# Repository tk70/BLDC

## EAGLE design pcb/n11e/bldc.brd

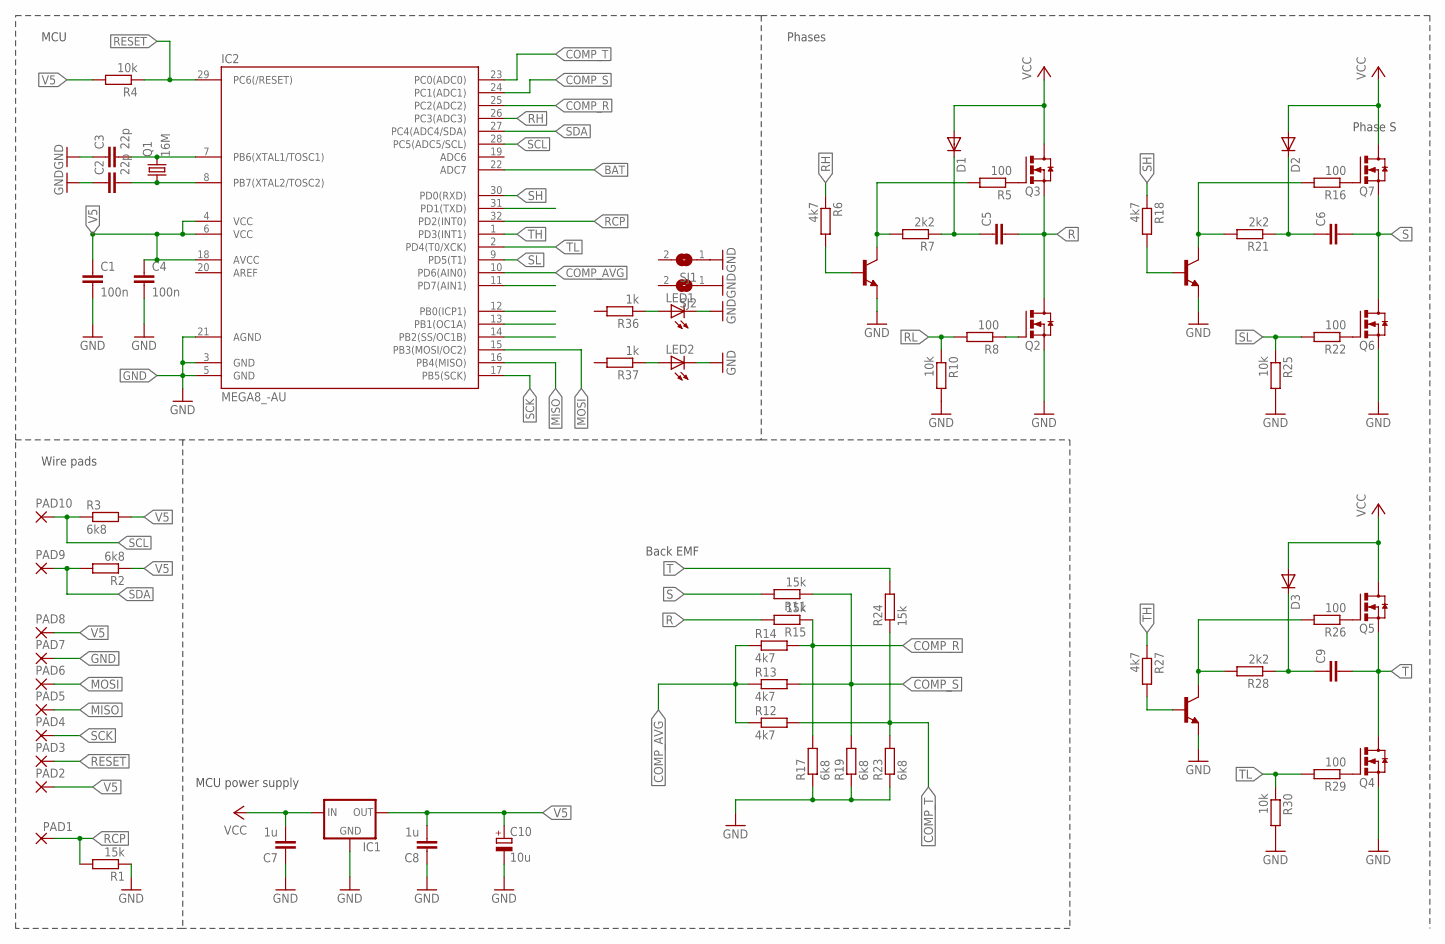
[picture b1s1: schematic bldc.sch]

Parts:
C1, C4: 100n; C0805K
C2, C3: 22p; C0805K
C5, C6, C9: C-EUC1206K; C1206K
C7, C8: 1u; C0805K
C10: 10u; E2,5RE
D1, D2, D3: 1N4148SOD-80; C1206K
IC1: LM1117TO252; TO252
IC2: MEGA8_-AU; TQFP32-08
LED1, LED2: LEDCHIPLED_0805; CHIPLED_0805
PAD1, PAD2, PAD3, PAD4, PAD5, PAD6, PAD7, PAD8, PAD9, PAD10: WIREPADSMD1,27-254; SMD1,27-2,54
Q1: 16M; SM49
Q2, Q3, Q4, Q5, Q6, Q7: IRFR1205; D-PAK_TO252AA
R1, R11, R24: 15k; R0603
R2, R3, R17, R19, R23: 6k8; R0603
R4, R10, R25, R30: 10k; R0603
R5, R8, R16, R22, R26, R29: 100; R0603
R6, R12, R13, R14, R18, R27: 4k7; R0603
R7, R21, R28: 2k2; R0603
R15: 15k; R0805
R36, R37: 1k; R0603
SJ1, SJ2: SJ
T1, T2, T3: BC847; SOT23

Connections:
BAT: IC2.22 (ADC7)
COMP_AVG: IC2.10 (PD6(AIN0)), R12.1, R13.1, R14.1
COMP_R: IC2.25 (PC2(ADC2)), R14.2, R15.1, R17.2
COMP_S: IC2.24 (PC1(ADC1)), R11.1, R13.2, R19.2
COMP_T: IC2.23 (PC0(ADC0)), R12.2, R23.2, R24.1
GND: C1.2, C2.1, C3.1, C4.2, C7.1, C8.1, C10.-, IC1.1 (GND), IC2.3 (GND), IC2.5 (GND), IC2.21 (AGND), LED1.C, LED2.C, PAD7.1, Q2.3 (S), Q4.3 (S), Q6.3 (S), R1.1, R10.2, R17.1, R19.1, R23.1, R25.2, R30.2, SJ1.1, SJ2.1, T1.2 (E), T2.2 (E), T3.2 (E)
MISO: IC2.16 (PB4(MISO)), PAD5.1
MOSI: IC2.15 (PB3(MOSI/OC2)), PAD6.1
unnamed: R6.2, T1.1 (B)
unnamed: C5.1, D1.2 (C), R7.1
unnamed: Q3.1 (G), R5.1
unnamed: R5.2, R7.2, T1.3 (C)
unnamed: Q6.1 (G), R22.1
unnamed: R18.2, T2.1 (B)
unnamed: C6.1, D2.2 (C), R21.1
unnamed: Q4.1 (G), R29.1
unnamed: Q2.1 (G), R8.1
unnamed: Q7.1 (G), R16.1
unnamed: R16.2, R21.2, T2.3 (C)
unnamed: R27.2, T3.1 (B)
unnamed: C9.1, D3.2 (C), R28.1
unnamed: R26.2, R28.2, T3.3 (C)
unnamed: Q5.1 (G), R26.1
unnamed: C2.2, IC2.8 (PB7(XTAL2/TOSC2)), Q1.1
unnamed: C3.2, IC2.7 (PB6(XTAL1/TOSC1)), Q1.2
unnamed: LED2.A, R37.1
unnamed: LED1.A, R36.1
R: C5.2, Q2.4 (D), Q3.3 (S), R15.2
RCP: IC2.32 (PD2(INT0)), PAD1.1, R1.2
RESET: IC2.29 (PC6(/RESET)), PAD3.1, R4.1
RH: IC2.26 (PC3(ADC3)), R6.1
RL: R8.2, R10.1
S: C6.2, Q6.4 (D), Q7.3 (S), R11.2
SCK: IC2.17 (PB5(SCK)), PAD4.1
SCL: IC2.28 (PC5(ADC5/SCL)), PAD10.1, R3.1
SDA: IC2.27 (PC4(ADC4/SDA)), PAD9.1, R2.2
SH: IC2.30 (PD0(RXD)), R18.1
SL: IC2.9 (PD5(T1)), R22.2, R25.1
T: C9.2, Q4.4 (D), Q5.3 (S), R24.2
TH: IC2.1 (PD3(INT1)), R27.1
TL: IC2.2 (PD4(T0/XCK)), R29.2, R30.1
V5: C1.1, C4.1, C8.2, C10.+, IC1.3 (OUT), IC2.4 (VCC), IC2.6 (VCC), IC2.18 (AVCC), PAD2.1, PAD8.1, R2.1, R3.2, R4.2
VCC: C7.2, D1.1 (A), D2.1 (A), D3.1 (A), IC1.2 (IN), Q3.4 (D), Q5.4 (D), Q7.4 (D)

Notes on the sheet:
Back EMF
MCU power supply
Phase S
Phases
MCU
Wire pads

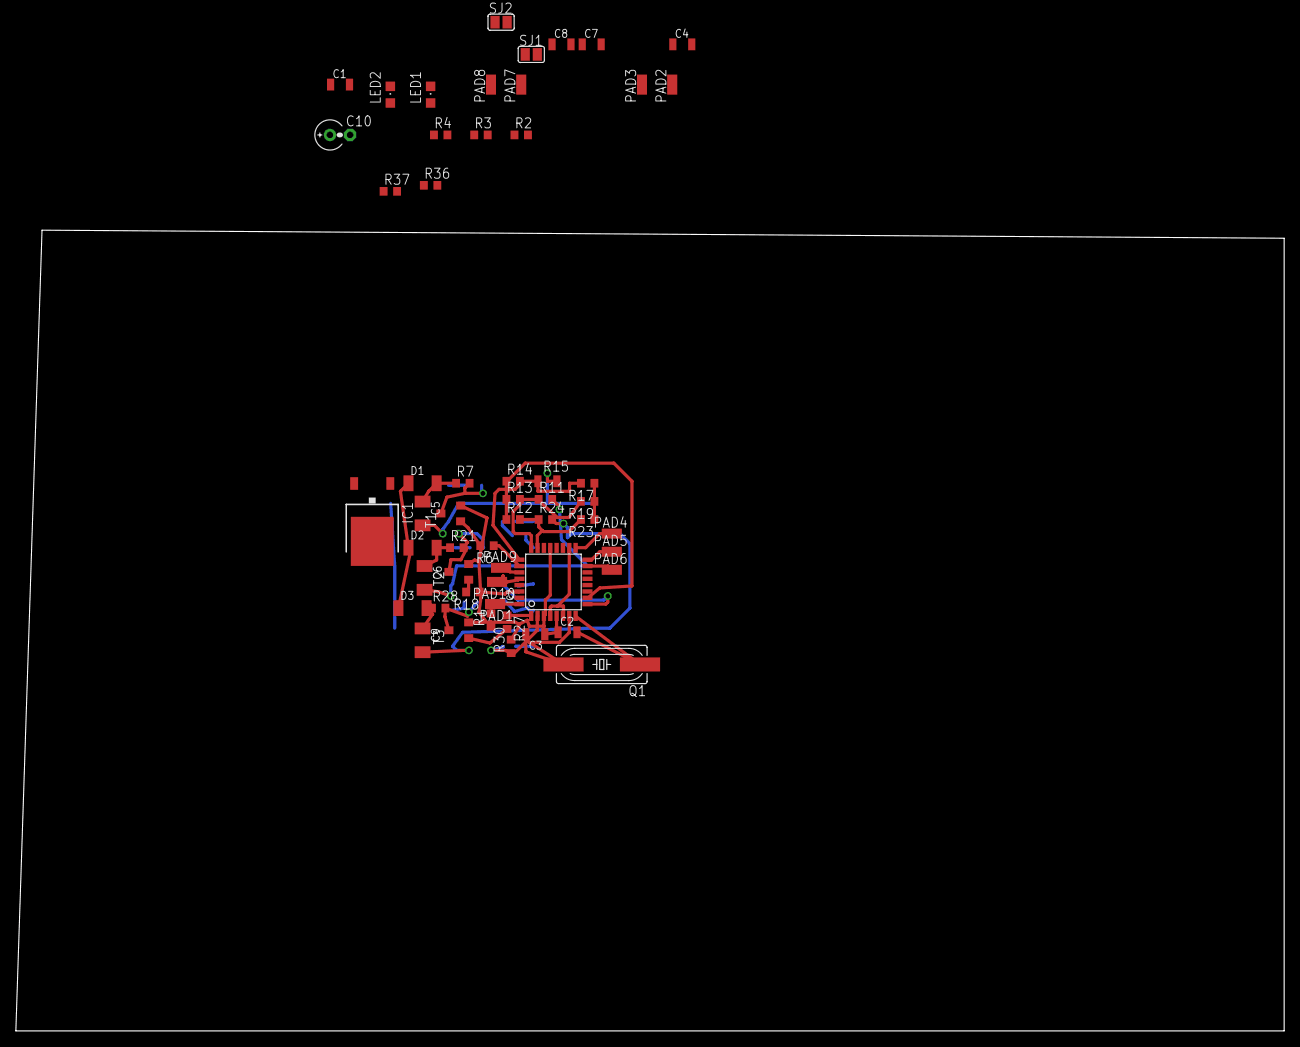
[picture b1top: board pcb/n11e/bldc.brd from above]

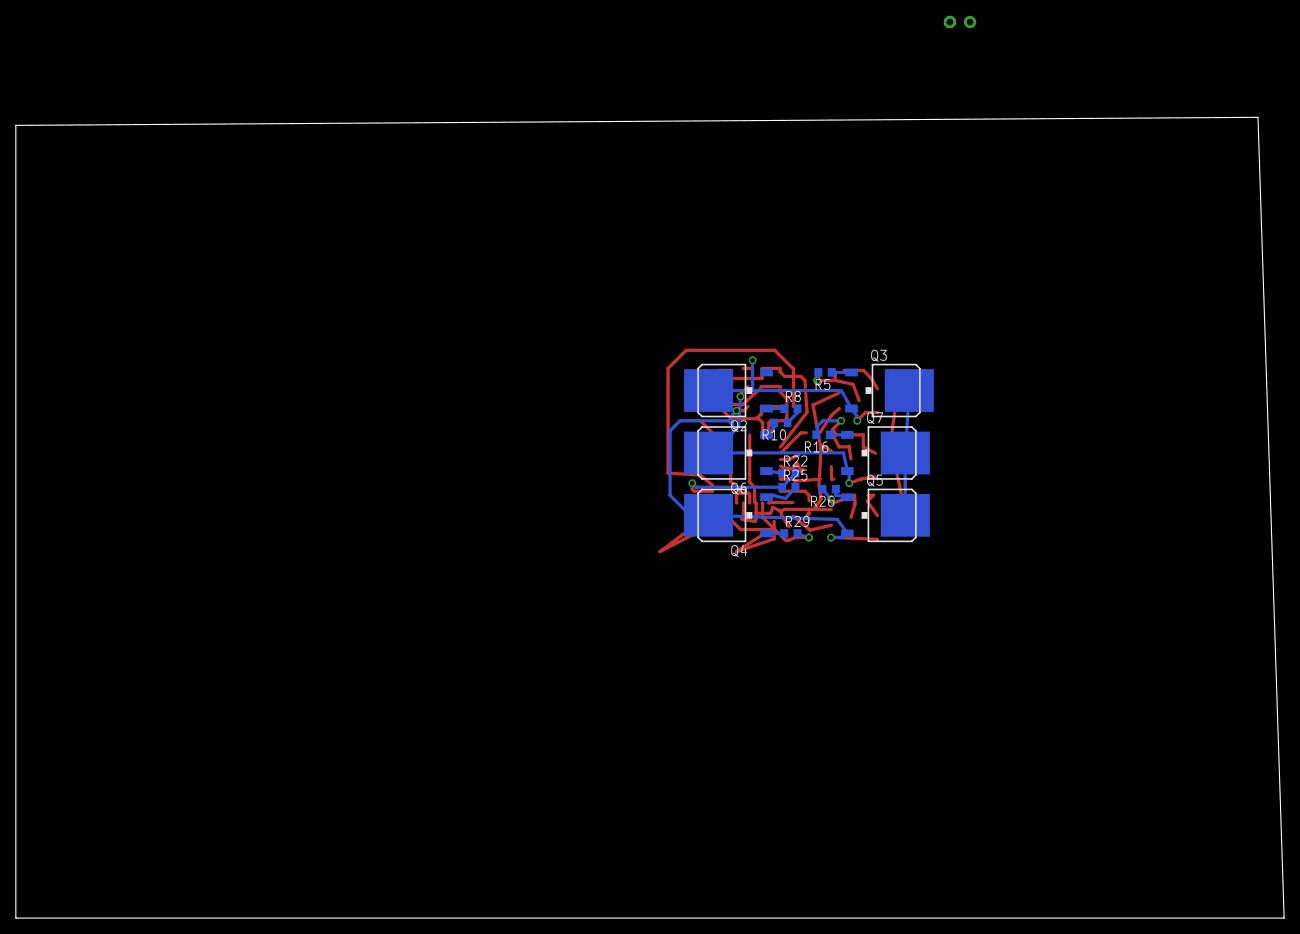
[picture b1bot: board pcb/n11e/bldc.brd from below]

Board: 2 copper layers, 160.0 x 101.0 mm, 69 parts (14 on the bottom side), 42 nets.

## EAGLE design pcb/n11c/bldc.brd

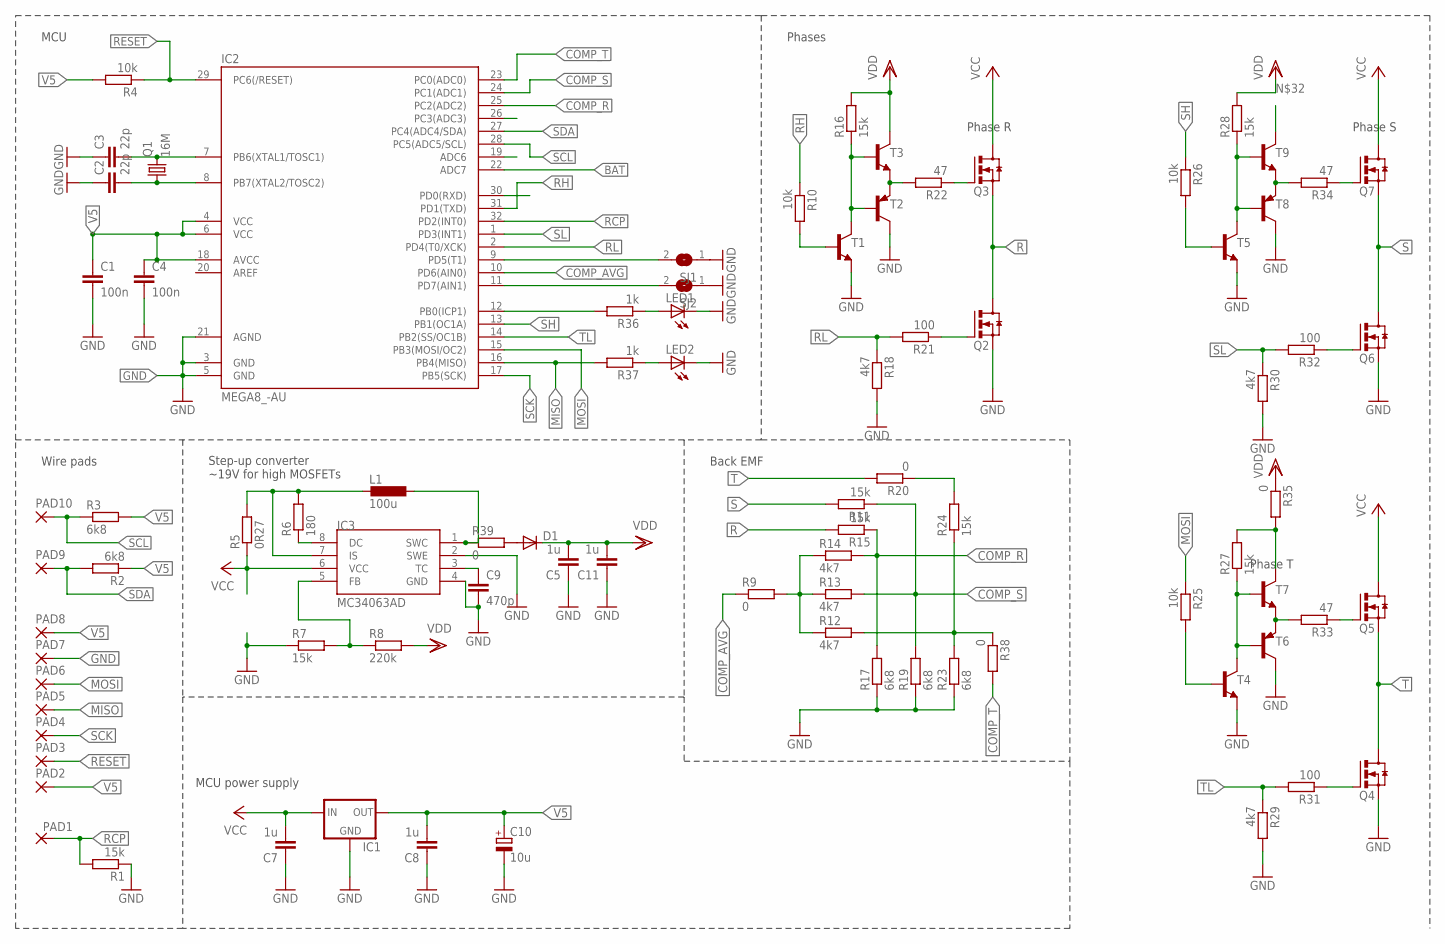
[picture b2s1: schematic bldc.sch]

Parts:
C1, C4: 100n; C0805K
C2, C3: 22p; C0805K
C5, C7, C8, C11: 1u; C0805K
C9: 470p; C0805K
C10: 10u; E2,5RE
D1: DIODE-SOD80C; SOD80C
IC1: LM1117TO252; TO252
IC2: MEGA8_-AU; TQFP32-08
IC3: MC34063AD; SOIC8
L1: 100u; 0204/7
LED1, LED2: LEDCHIPLED_0805; CHIPLED_0805
PAD1, PAD2, PAD3, PAD4, PAD5, PAD6, PAD7, PAD8, PAD9, PAD10: WIREPADSMD1,27-254; SMD1,27-2,54
Q1: 16M; SM49
Q2, Q3, Q4, Q5, Q6, Q7: IRFR1205; D-PAK_TO252AA
R1, R7, R11, R15, R16, R24, R27, R28: 15k; R0805
R2, R3, R17, R19, R23: 6k8; R0805
R4, R10, R25, R26: 10k; R0805
R5: 0R27; R0805
R6: 180; R0805
R8: 220k; R0805
R9, R38, R39: 0; R0805
R12, R13, R14, R18, R29, R30: 4k7; R0805
R20, R35: 0; R1206
R21, R31, R32: 100; R0805
R22, R33, R34: 47; R0805
R36, R37: 1k; R0805
SJ1, SJ2: SJ
T1, T3, T4, T5, T7, T9: BC847; SOT23
T2, T6, T8: BC807-16-PNP-SOT23-BEC; SOT23-BEC

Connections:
BAT: IC2.22 (ADC7)
COMP_AVG: IC2.10 (PD6(AIN0)), R9.1
COMP_R: IC2.25 (PC2(ADC2)), R14.2, R15.1, R17.2
COMP_S: IC2.24 (PC1(ADC1)), R11.1, R13.2, R19.2
COMP_T: IC2.23 (PC0(ADC0)), R38.2
GND: C1.2, C2.1, C3.1, C4.2, C5.1, C7.1, C8.1, C9.2, C10.-, C11.1, IC1.1 (GND), IC2.3 (GND), IC2.5 (GND), IC2.21 (AGND), IC3.2 (SWE), IC3.4 (GND), LED1.C, LED2.C, PAD7.1, Q2.3 (S), Q4.3 (S), Q6.3 (S), R1.1, R7.1, R17.1, R18.2, R19.1, R23.1, R29.2, R30.2, SJ1.1, SJ2.1, T1.2 (E), T2.C, T4.2 (E), T5.2 (E), T6.C, T8.C
MISO: IC2.16 (PB4(MISO)), PAD5.1, R37.2
MOSI: IC2.15 (PB3(MOSI/OC2)), PAD6.1, R25.1
unnamed: R10.2, T1.1 (B)
unnamed: R9.2, R12.1, R13.1, R14.1
unnamed: R16.1, T1.3 (C), T2.B, T3.1 (B)
unnamed: Q3.1 (G), R22.1
unnamed: R22.2, T2.E, T3.2 (E)
unnamed: Q4.1 (G), R31.1
unnamed: Q2.1 (G), R21.1
unnamed: Q6.1 (G), R32.1
unnamed: IC3.5 (FB), R7.2, R8.1
unnamed: IC3.8 (DC), R6.1
unnamed: IC3.1 (SWC), L1.1, R39.1
unnamed: IC3.7 (IS), L1.2, R5.2, R6.2
unnamed: R28.1, T5.3 (C), T8.B, T9.1 (B)
unnamed: C2.2, IC2.8 (PB7(XTAL2/TOSC2)), Q1.1
unnamed: C3.2, IC2.7 (PB6(XTAL1/TOSC1)), Q1.2
unnamed: Q7.1 (G), R34.1
unnamed: R34.2, T8.E, T9.2 (E)
unnamed: R26.2, T5.1 (B)
unnamed: Q5.1 (G), R33.1
unnamed: R20.1, R24.2
unnamed: R27.1, T4.3 (C), T6.B, T7.1 (B)
unnamed: R33.2, T6.E, T7.2 (E)
unnamed: R27.2, R35.2, T7.3 (C), T9.3 (C)
unnamed: IC2.12 (PB0(ICP1)), R36.2
unnamed: IC2.11 (PD7(AIN1)), SJ2.2
unnamed: R25.2, T4.1 (B)
unnamed: IC2.9 (PD5(T1)), SJ1.2
unnamed: LED2.A, R37.1
unnamed: LED1.A, R36.1
unnamed: R12.2, R23.2, R24.1, R38.1
unnamed: C9.1, IC3.3 (TC)
unnamed: D1.A, R39.2
R: Q2.4 (D), Q3.3 (S), R15.2
RCP: IC2.32 (PD2(INT0)), PAD1.1, R1.2
RESET: IC2.29 (PC6(/RESET)), PAD3.1, R4.1
RH: IC2.31 (PD1(TXD)), R10.1
RL: IC2.2 (PD4(T0/XCK)), R18.1, R21.2
S: Q6.4 (D), Q7.3 (S), R11.2
SCK: IC2.17 (PB5(SCK)), PAD4.1
SCL: IC2.28 (PC5(ADC5/SCL)), PAD10.1, R3.1
SDA: IC2.27 (PC4(ADC4/SDA)), PAD9.1, R2.2
SH: IC2.13 (PB1(OC1A)), R26.1
SL: IC2.1 (PD3(INT1)), R30.1, R32.2
T: Q4.4 (D), Q5.3 (S), R20.2
TL: IC2.14 (PB2(SS/OC1B)), R29.1, R31.2
V5: C1.1, C4.1, C8.2, C10.+, IC1.3 (OUT), IC2.4 (VCC), IC2.6 (VCC), IC2.18 (AVCC), PAD2.1, PAD8.1, R2.1, R3.2, R4.2
VCC: C7.2, IC1.2 (IN), IC3.6 (VCC), Q3.4 (D), Q5.4 (D), Q7.4 (D), R5.1
VDD: C5.2, C11.2, D1.C, R8.2, R16.2, R28.2, R35.1, T3.3 (C)

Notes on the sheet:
Phase R
Step-up converter ~19V for high MOSFETs
Back EMF
MCU power supply
Phase S
Phase T
Phases
MCU
Wire pads

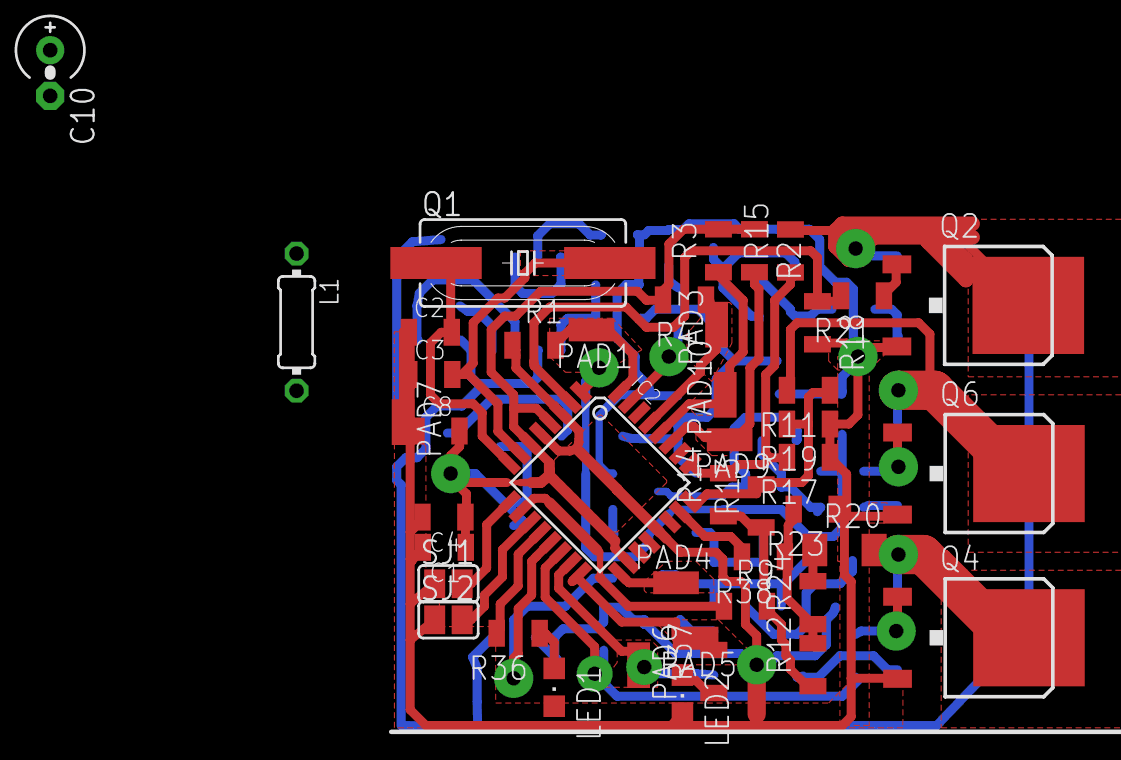
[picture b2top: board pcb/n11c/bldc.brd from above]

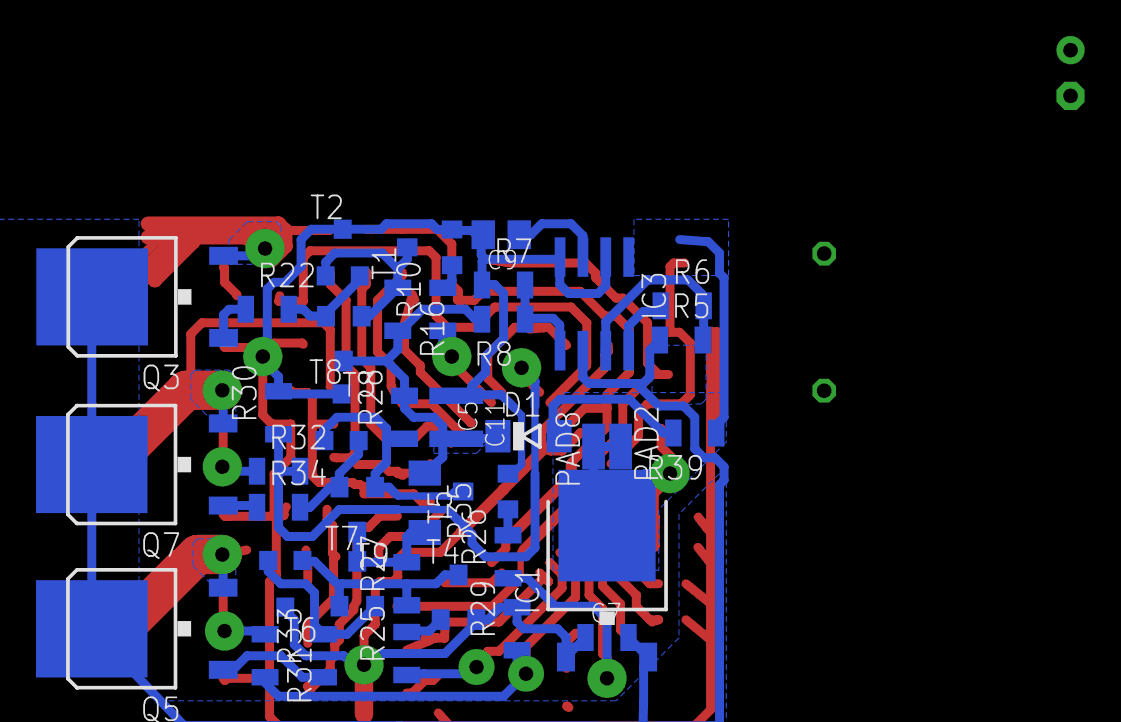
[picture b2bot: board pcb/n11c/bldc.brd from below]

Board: 3 copper layers, 84 parts (40 on the bottom side), 55 nets.

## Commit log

2013-09-28 Added all files
2013-10-05 led stuff, beeps
    the timer freezes sometiems if used after power on
2013-11-07 calculations in background
2013-11-13 started i2c implementation
2013-11-15 fixed division
2013-11-19 fixed sync loss on low rpm
2013-11-27 working on i2c protocol
2013-11-30 start up step
2014-02-27 support for inverting pins
2014-03-12 speed-power limit, governor
2014-06-13 moved sdm to timer2, throttle rising speed limited
2014-06-14 added I control
2014-06-15 governor: added anti-windup, error dead zone
2014-09-12 Rearranged repo folders
2014-09-12 Added PCB eagle files
2014-09-12 fix: solution files
2014-09-12 Removed .atsuo file from the index
2014-12-06 new board
